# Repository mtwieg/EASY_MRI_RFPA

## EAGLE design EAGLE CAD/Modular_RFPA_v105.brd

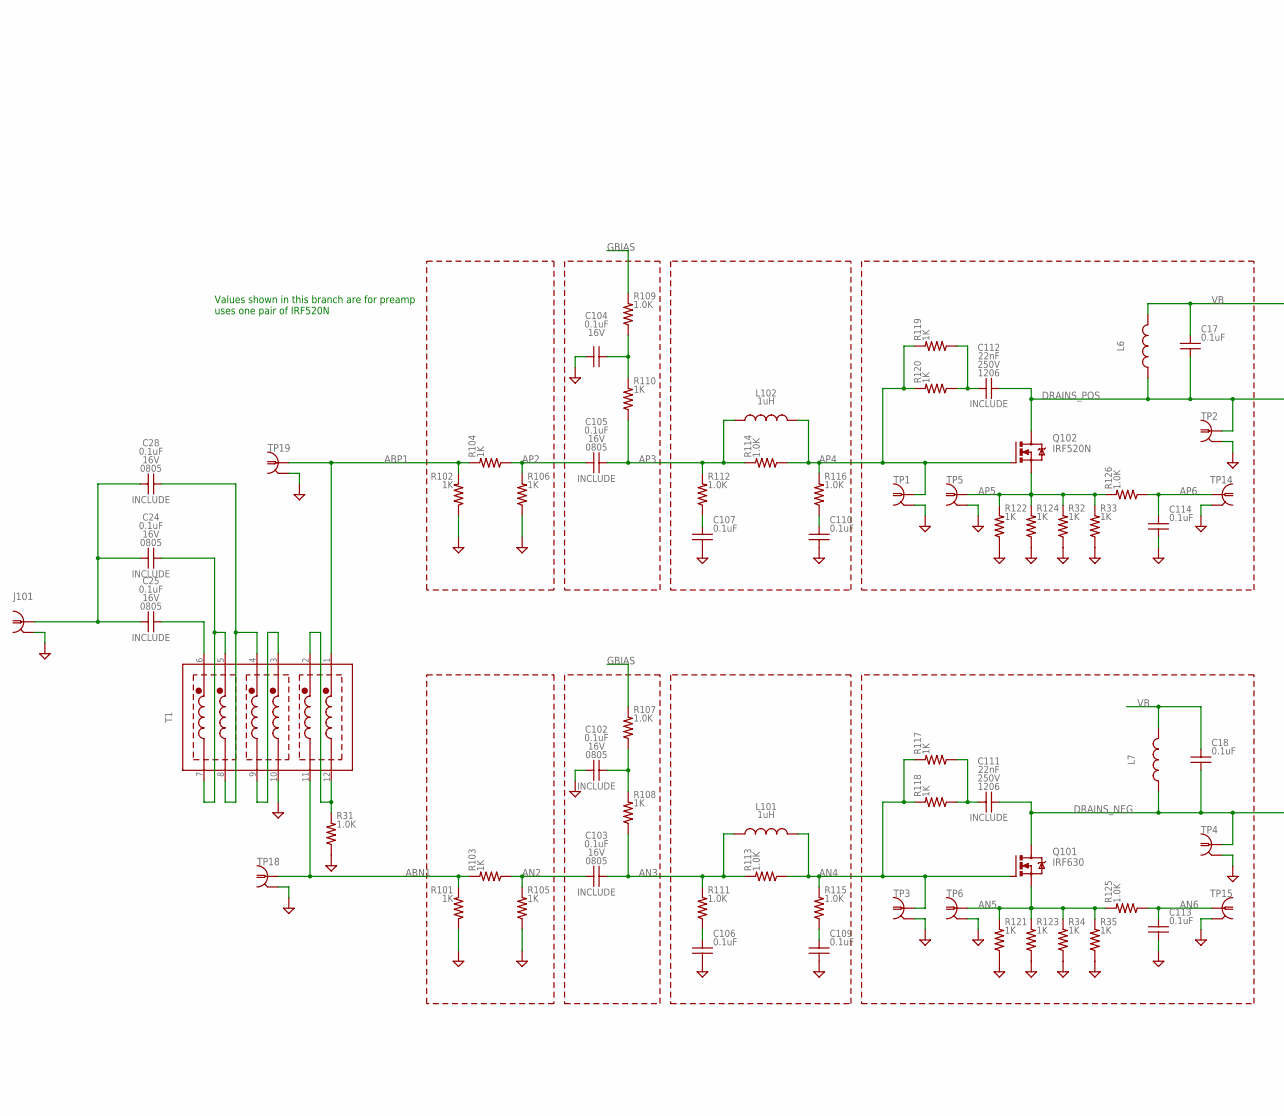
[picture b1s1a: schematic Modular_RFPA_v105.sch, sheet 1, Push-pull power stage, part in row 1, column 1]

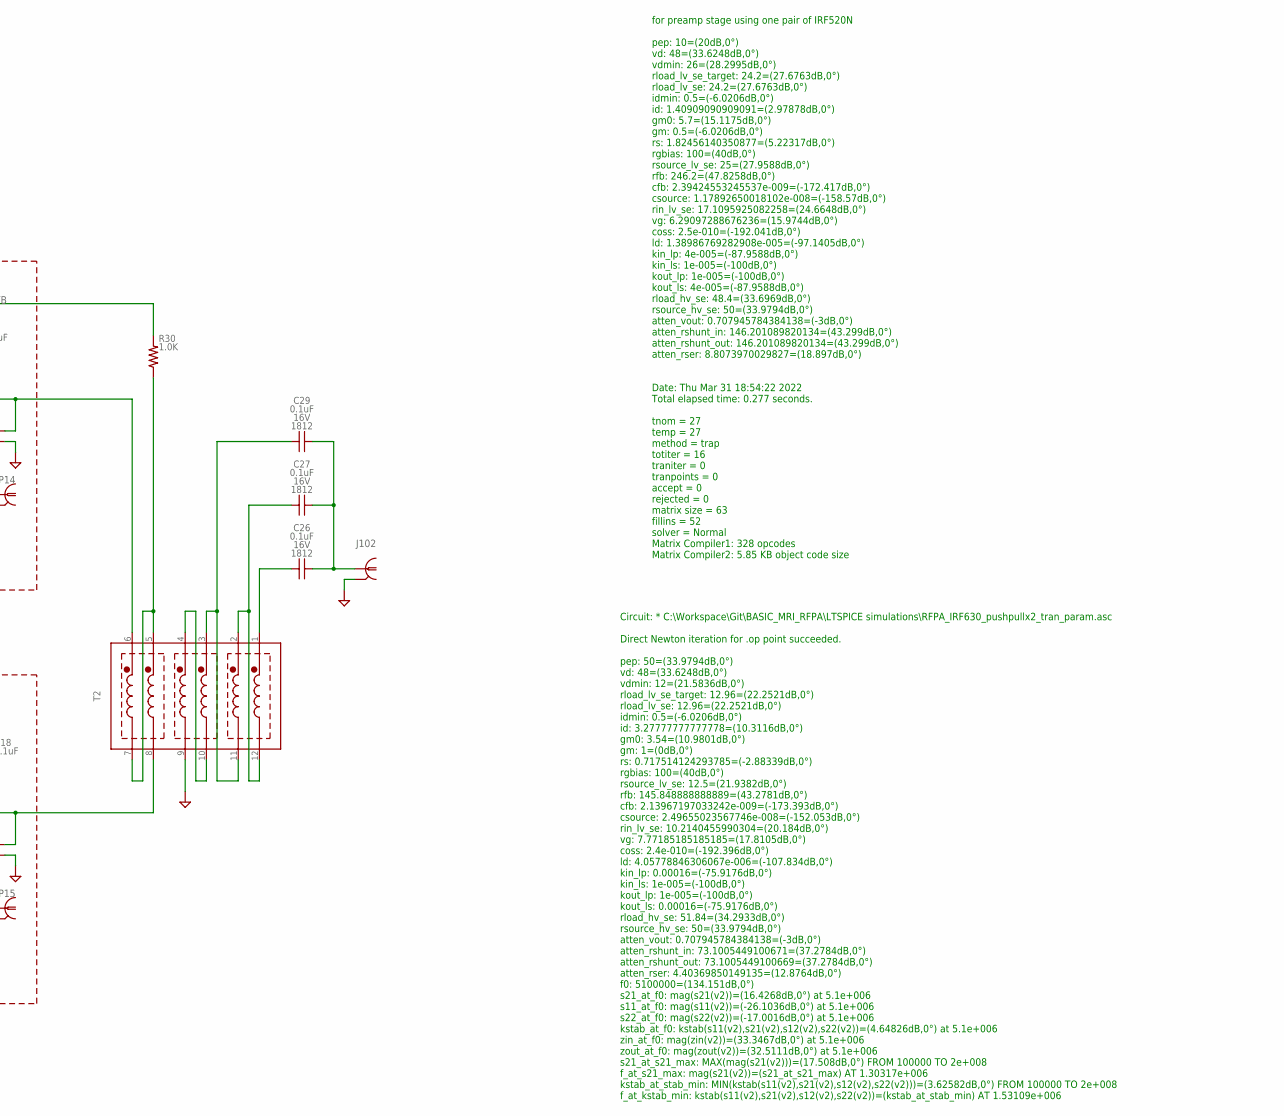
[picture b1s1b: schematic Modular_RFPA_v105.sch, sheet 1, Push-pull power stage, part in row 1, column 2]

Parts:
C17, C18, C26, C27, C29: 0.1uF; C1812
C24, C25, C28, C102, C103, C104, C105, C106, C107, C109, C110, C113, C114: 0.1uF; 0805_IPC-7351B
C111, C112: 22nF; C1206
J101, J102: COAXBNC_EDGE; BNC_EDGE
L6, L7: L; DR127
L101, L102: 1uH; L1008
Q101: IRF630; TO220BV
Q102: IRF520N; TO220BV
R30, R31, R107, R109, R111, R112, R113, R114, R115, R116, R125, R126: 1.0K; 0805_IPC-7351B
R32, R33, R34, R35, R117, R118, R119, R120, R121, R122, R123, R124: 1K; R2512
R101, R102, R103, R104, R105, R106, R108, R110: 1K; R1206
T1, T2: HP4_TRAFO; HP4
TP1, TP3, TP14, TP15, TP18, TP19: PROBE_TPTP_5MM; PROBE_TP_5MM
TP2, TP4, TP5, TP6: PROBE_TPTP_7P5MM; PROBE_TP_7P5MM

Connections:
ABN1: R101.1, R103.1, T1.11 (F2), TP18.TP (1); also elsewhere on the board
ABP1: R102.1, R104.1, T1.1 (S1), TP19.TP (1); also elsewhere on the board
AN2: C103.2, R103.2, R105.1
AN3: C103.1, L101.1, R108.2, R111.1, R113.1
AN4: L101.2, Q101.G, R113.2, R115.1, R117.1, R118.1, TP3.TP (1)
AN5: Q101.S, R34.1, R35.1, R121.1, R123.1, R125.1, TP6.TP (1)
AN6: C113.1, R125.2, TP15.TP (1)
AP2: C105.2, R104.2, R106.1
AP3: C105.1, L102.1, R110.2, R112.1, R114.1
AP4: L102.2, Q102.G, R114.2, R116.1, R119.1, R120.1, TP1.TP (1)
AP5: Q102.S, R32.1, R33.1, R122.1, R124.1, R126.1, TP5.TP (1)
AP6: C114.1, R126.2, TP14.TP (1)
DRAINS_NEG: C18.2, C111.2, L7.1, Q101.D, T2.8 (F5), TP4.TP (1); also elsewhere on the board
DRAINS_POS: C17.2, C112.2, L6.1, Q102.D, T2.6 (S6), TP2.TP (1); also elsewhere on the board
GBIAS: R107.1, R109.1; also elsewhere on the board
GND: C102.2, C104.2, C106.2, C107.2, C109.2, C110.2, C113.2, C114.2, J101.G1 (GND1), J101.G2 (GND1), J101.G3 (GND1), J101.G4 (GND1), J102.G1 (GND1), J102.G2 (GND1), J102.G3 (GND1), J102.G4 (GND1), R31.2, R32.2, R33.2, R34.2, R35.2, R101.2, R102.2, R105.2, R106.2, R121.2, R122.2, R123.2, R124.2, T1.10 (F3), T2.9 (F4), TP1.GND (GND1), TP2.GND (GND1), TP3.GND (GND1), TP4.GND (GND1), TP5.GND (GND1), TP6.GND (GND1), TP14.GND (GND1), TP15.GND (GND1), TP18.GND (GND1), TP19.GND (GND1); also elsewhere on the board
unnamed: C111.1, R117.2, R118.2
unnamed: C106.1, R111.2
unnamed: C104.1, R109.2, R110.1
unnamed: C107.1, R112.2
unnamed: C110.1, R116.2
unnamed: C112.1, R119.2, R120.2
unnamed: C102.1, R107.2, R108.1
unnamed: C109.1, R115.2
unnamed: T1.3 (S3), T1.9 (F4)
unnamed: R31.1, T1.2 (S2), T1.12 (F1)
unnamed: C27.1, T2.2 (S2), T2.12 (F1)
unnamed: C26.1, T2.1 (S1)
unnamed: C26.2, C27.2, C29.2, J102.C (1)
unnamed: C24.2, C25.2, C28.2, J101.C (1)
unnamed: C25.1, T1.6 (S6)
unnamed: C29.1, T2.3 (S3), T2.11 (F2)
unnamed: C28.1, T1.4 (S4), T1.8 (F5)
unnamed: T2.4 (S4), T2.10 (F3)
VB: C17.1, C18.1, L6.2, L7.2, R30.1; also elsewhere on the board
VB_CT: R30.2, T2.5 (S5), T2.7 (F6)
VB_CT1: C24.1, T1.5 (S5), T1.7 (F6)

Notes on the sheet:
for preamp stage using one pair of IRF520N pep: 10=(20dB,0°) vd: 48=(33.6248dB,0°) vdmin: 26=(28.2995dB,0°) rload_lv_se_target: 24.2=(27.6763dB,0°) rload_lv_se: 24.2=(27.6763dB,0°) idmin: 0.5=(-6.0206dB,0°) id: 1.40909090909091=(2.97878dB,0°) gm0: 5.7=(15.1175dB,0°) gm: 0.5=(-6.0206dB,0°) rs: 1.824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
Values shown in this branch are for preamp uses one pair of IRF520N
Circuit: * C:\Workspace\Git\BASIC_MRI_RFPA\LTSPICE simulations\RFPA_IRF630_pushpullx2_tran_param.asc Direct Newton iteration for .op point succeeded. pep: 50=(33.9794dB,0°) vd: 48=(33.6248dB,0°) vdmin: 12=(21.5836dB,0°) rload_lv_se_target: 12.96=(22.2521dB,0°) rload_lv_se: 12.96=(22.2521dB,0°) idmi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

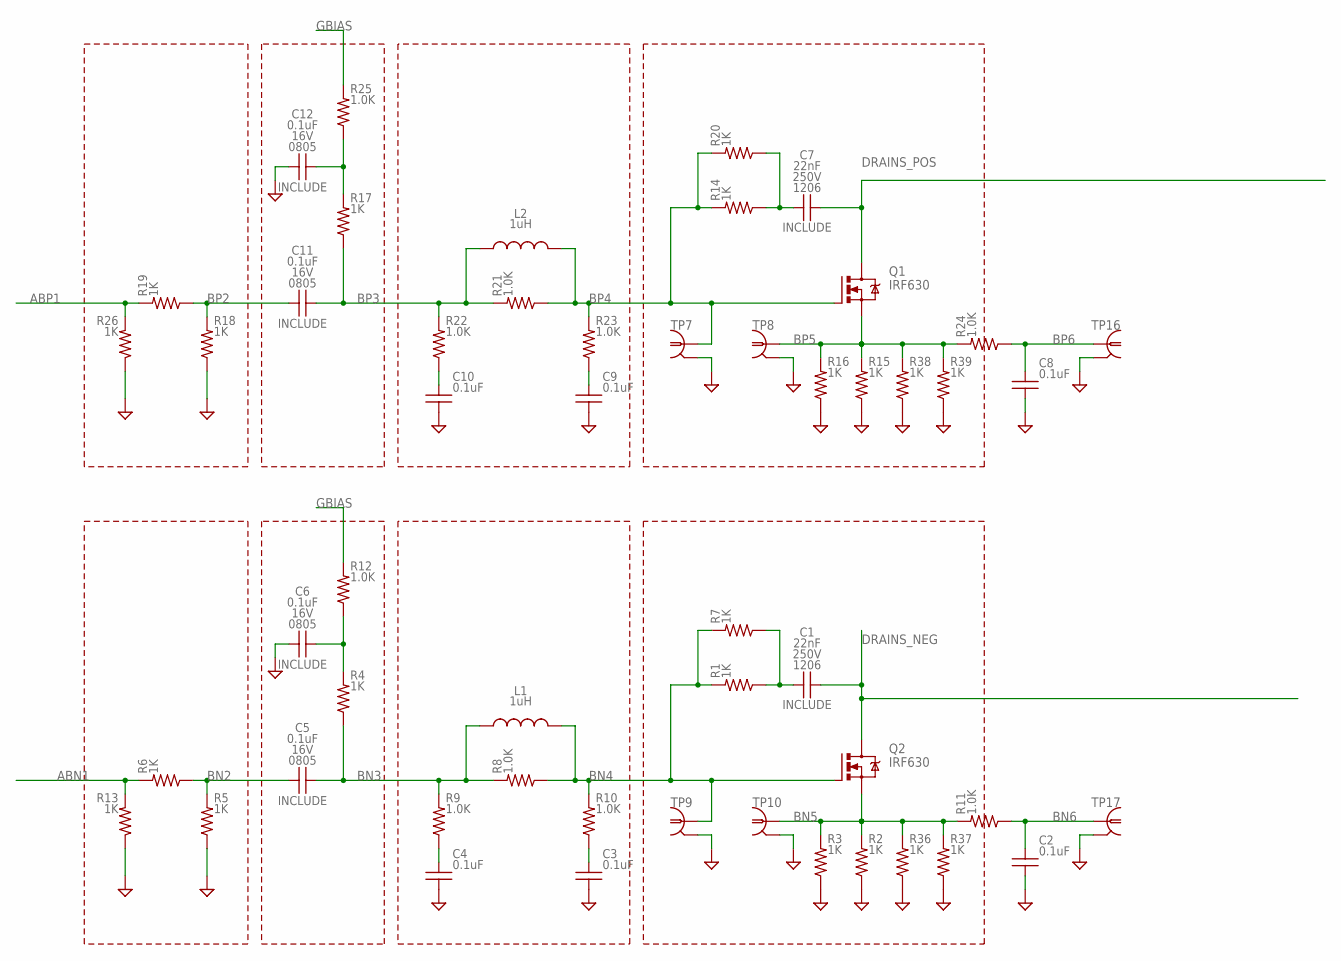
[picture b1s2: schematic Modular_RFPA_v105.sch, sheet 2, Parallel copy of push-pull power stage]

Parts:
C1, C7: 22nF; C1206
C2, C3, C4, C5, C6, C8, C9, C10, C11, C12: 0.1uF; 0805_IPC-7351B
L1, L2: 1uH; L1008
Q1, Q2: IRF630; TO220BV
R1, R2, R3, R7, R14, R15, R16, R20, R36, R37, R38, R39: 1K; R2512
R4, R5, R6, R13, R17, R18, R19, R26: 1K; R1206
R8, R9, R10, R11, R12, R21, R22, R23, R24, R25: 1.0K; 0805_IPC-7351B
TP7, TP9, TP10, TP16: PROBE_TPTP_5MM; PROBE_TP_5MM
TP8, TP17: PROBE_TPTP_7P5MM; PROBE_TP_7P5MM

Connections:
ABN1: R6.1, R13.1; also elsewhere on the board
ABP1: R19.1, R26.1; also elsewhere on the board
BN2: C5.2, R5.1, R6.2
BN3: C5.1, L1.1, R4.2, R8.1, R9.1
BN4: L1.2, Q2.G, R1.1, R7.1, R8.2, R10.1, TP9.TP (1)
BN5: Q2.S, R2.1, R3.1, R11.1, R36.1, R37.1, TP10.TP (1)
BN6: C2.1, R11.2, TP17.TP (1)
BP2: C11.2, R18.1, R19.2
BP3: C11.1, L2.1, R17.2, R21.1, R22.1
BP4: L2.2, Q1.G, R14.1, R20.1, R21.2, R23.1, TP7.TP (1)
BP5: Q1.S, R15.1, R16.1, R24.1, R38.1, R39.1, TP8.TP (1)
BP6: C8.1, R24.2, TP16.TP (1)
DRAINS_NEG: C1.2, Q2.D; also elsewhere on the board
DRAINS_POS: C7.2, Q1.D; also elsewhere on the board
GBIAS: R12.1, R25.1; also elsewhere on the board
GND: C2.2, C3.2, C4.2, C6.2, C8.2, C9.2, C10.2, C12.2, R2.2, R3.2, R5.2, R13.2, R15.2, R16.2, R18.2, R26.2, R36.2, R37.2, R38.2, R39.2, TP7.GND (GND1), TP8.GND (GND1), TP9.GND (GND1), TP10.GND (GND1), TP16.GND (GND1), TP17.GND (GND1); also elsewhere on the board
unnamed: C6.1, R4.1, R12.2
unnamed: C4.1, R9.2
unnamed: C3.1, R10.2
unnamed: C1.1, R1.2, R7.2
unnamed: C12.1, R17.1, R25.2
unnamed: C10.1, R22.2
unnamed: C9.1, R23.2
unnamed: C7.1, R14.2, R20.2

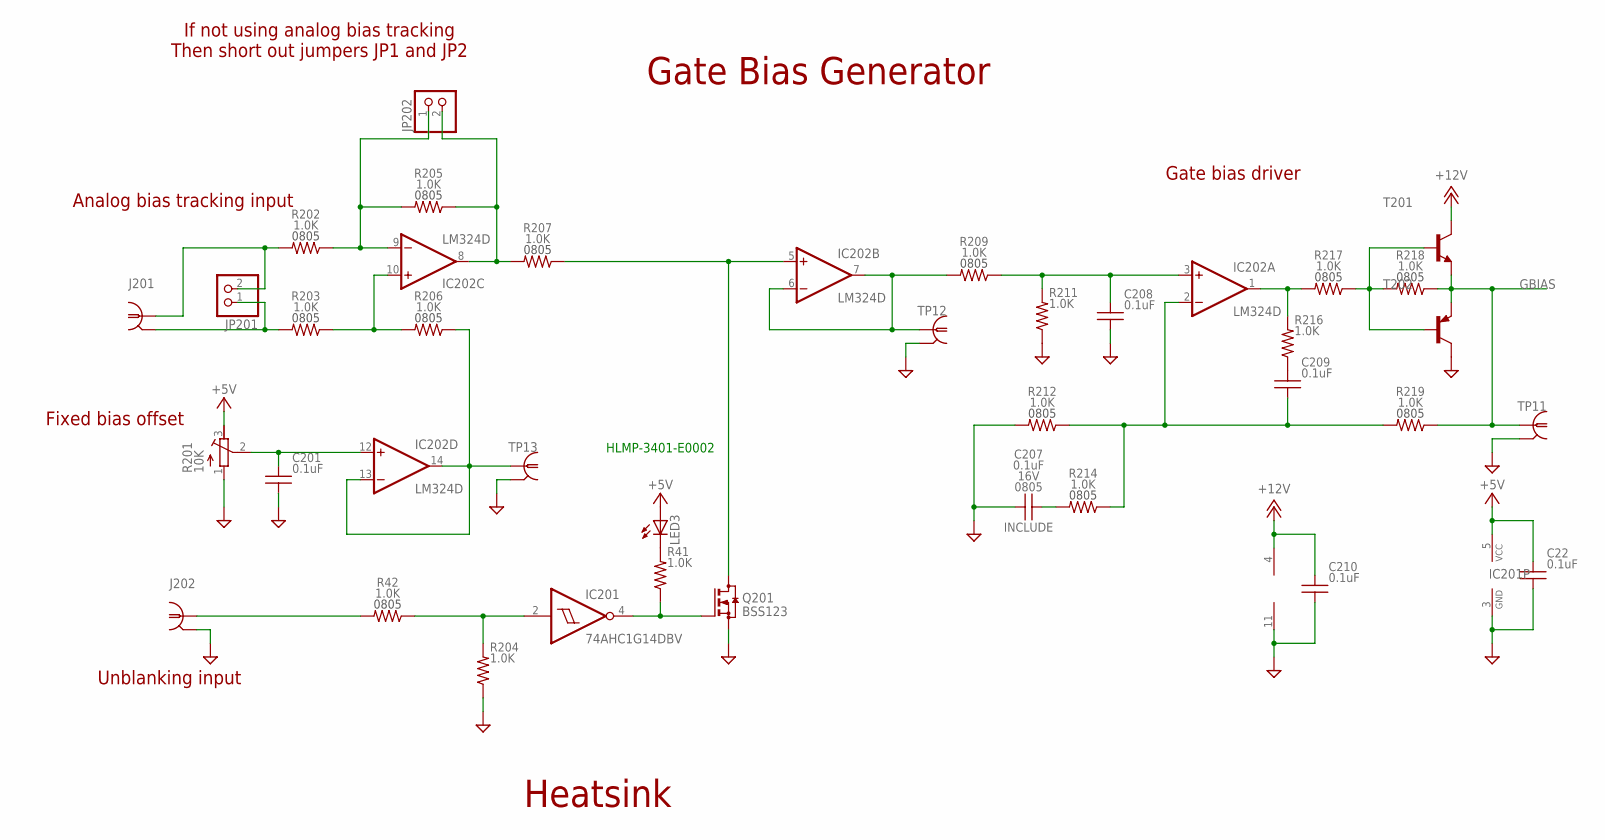
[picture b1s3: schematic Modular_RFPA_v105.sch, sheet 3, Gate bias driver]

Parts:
C22, C201, C207, C208, C209, C210: 0.1uF; 0805_IPC-7351B
IC201: 74AHC1G14DBV; SOT23-5
IC202: LM324D; SO14
J201, J202: COAXBNC_EDGE; BNC_EDGE
JP201, JP202: PINHD-1X2; 1X02
LED3: LED5MM
Q201: BSS123; SOT23
R41, R42, R202, R203, R204, R205, R206, R207, R209, R211, R212, R214, R216, R217, R218, R219: 1.0K; 0805_IPC-7351B
R201: 10K; RTRIM3299W
T201: BC808-NPN-SOT23-BEC; SOT23-BEC
T202: BC807-16-PNP-SOT23-BEC; SOT23-BEC
TP11, TP12, TP13: PROBE_TPTP_5MM; PROBE_TP_5MM

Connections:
+5V: C22.1, IC201.5 (VCC), LED3.A, R201.3 (E); also elsewhere on the board
+12V: C210.1, IC202.4 (V+), T201.C; also elsewhere on the board
GBIAS: R218.2, R219.2, T201.E, T202.E, TP11.TP (1); also elsewhere on the board
GND: C22.2, C201.2, C207.2, C208.2, C210.2, IC201.3 (GND), IC202.11 (V-), J202.G1 (GND1), J202.G2 (GND1), J202.G3 (GND1), J202.G4 (GND1), Q201.2 (S), R201.1 (A), R204.2, R211.2, R212.1, T202.C, TP11.GND (GND1), TP12.GND (GND1), TP13.GND (GND1); also elsewhere on the board
unnamed: IC202.1 (OUT), R216.1, R217.1
unnamed: R217.2, R218.1, T201.B, T202.B
unnamed: IC201.2 (I), R42.2, R204.1
unnamed: IC202.6 (-IN), IC202.7 (OUT), R209.1, TP12.TP (1)
unnamed: C209.1, R216.2
unnamed: C207.1, R214.1
unnamed: C209.2, IC202.2 (-IN), R212.2, R214.2, R219.1
unnamed: C208.1, IC202.3 (+IN), R209.2, R211.1
unnamed: IC202.10 (+IN), R203.2, R206.1
unnamed: IC202.8 (OUT), JP202.2, R205.2, R207.1
unnamed: IC202.9 (-IN), JP202.1, R202.2, R205.1
unnamed: J201.C (1), JP201.2, R202.1
unnamed: J201.G1 (GND1), J201.G2 (GND1), J201.G3 (GND1), J201.G4 (GND1), JP201.1, R203.1
unnamed: IC202.5 (+IN), Q201.3 (D), R207.2
unnamed: IC201.4 (O), Q201.1 (G), R41.2
unnamed: C201.1, IC202.12 (+IN), R201.2 (S)
unnamed: IC202.13 (-IN), IC202.14 (OUT), R206.2, TP13.TP (1)
unnamed: LED3.K (C), R41.1
unnamed: J202.C (1), R42.1

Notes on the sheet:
Gate Bias Generator
Heatsink
If not using analog bias tracking Then short out jumpers JP1 and JP2
Analog bias tracking input
Fixed bias offset
Gate bias driver
Unblanking input
‎HLMP-3401-E0002‎

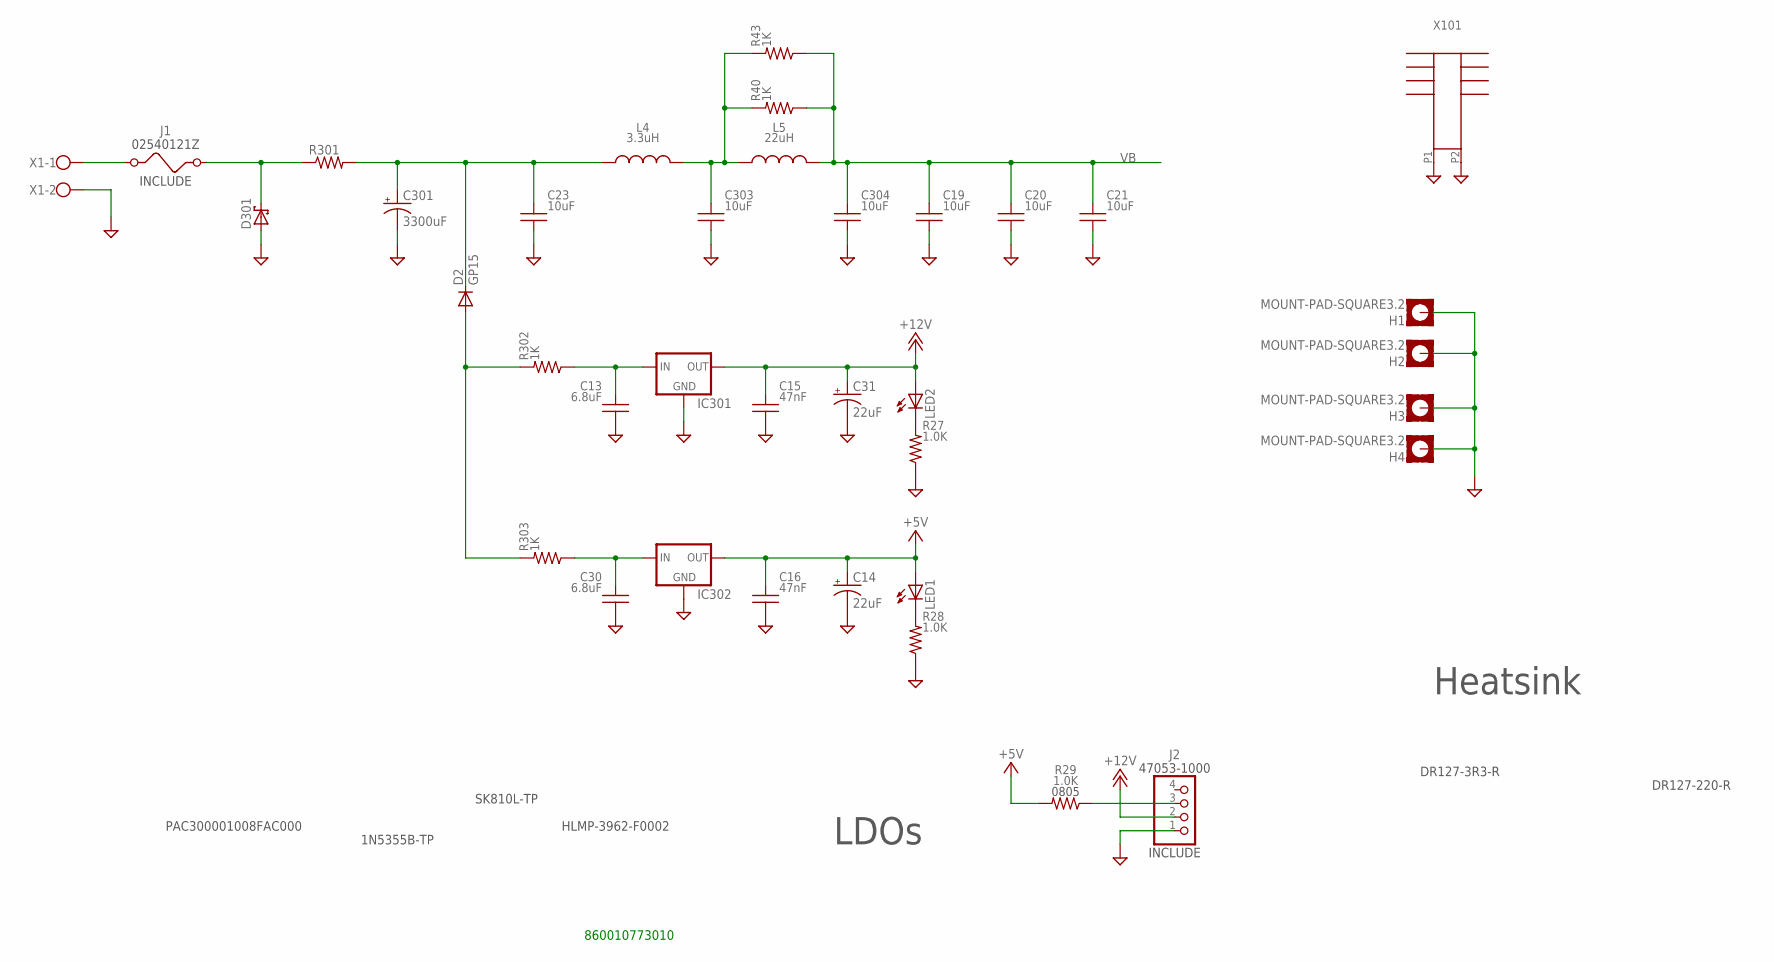
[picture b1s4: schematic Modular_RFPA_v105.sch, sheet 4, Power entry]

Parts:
C13, C30: 6.8uF; C1210
C14, C31: 22uF; E2,5-7
C15, C16: 47nF; C1206
C19, C20, C21, C23, C303, C304: 10uF; C2220_CKG57N
C301: 3300uF; EB25D
D2: GP15; DO15-12
D301: SCHOTTKY-DIODESMC; SMC
H1, H2, H3, H4: MOUNT-PAD-SQUARE3.2; 3,2-PAD-SQUARE
IC301, IC302: 78XXS
J1: FUSE_2P; 02540121Z
J2: KK_PCFAN; 47053-1000
L4: 3.3uH; DR127
L5: 22uH; DR127
LED1, LED2: LED5MM
R27, R28, R29: 1.0K; 0805_IPC-7351B
R40, R43, R302, R303: 1K; R1206
R301: R-US_0817/7V; P0817V
X1: W237-102
X101: HEATSINK_OMNI_DUAL30-75-D; OMNI-UNI-30-75-D

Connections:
+5V: C14.+, C16.1, IC302.OUT, LED1.A, R29.1; also elsewhere on the board
+12V: C15.1, C31.+, IC301.OUT, J2.2, LED2.A; also elsewhere on the board
GND: C13.2, C14.-, C15.2, C16.2, C19.2, C20.2, C21.2, C23.2, C30.2, C31.-, C301.-, C303.2, C304.2, D301.A, H1.B3,2, H2.B3,2, H3.B3,2, H4.B3,2, IC301.GND, IC302.GND, J2.1, R27.2, R28.2, X1.2, X101.P1, X101.P2; also elsewhere on the board
unnamed: D2.A, R302.1, R303.1
unnamed: LED2.K (C), R27.1
unnamed: LED1.K (C), R28.1
unnamed: C13.1, IC301.IN, R302.2
unnamed: D301.C, J1.2, R301.1
unnamed: J1.1, X1.1
unnamed: C23.1, C301.+, D2.C, L4.1, R301.2
unnamed: C303.1, L4.2, L5.1, R40.1, R43.1
unnamed: C30.1, IC302.IN, R303.2
unnamed: J2.3, R29.2
VB: C19.1, C20.1, C21.1, C304.1, L5.2, R40.2, R43.2; also elsewhere on the board

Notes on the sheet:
LDOs
Heatsink
PAC300001008FAC000
DR127-220-R
DR127-3R3-R
1N5355B-TP
HLMP-3962-F0002‎
860010773010
SK810L-TP

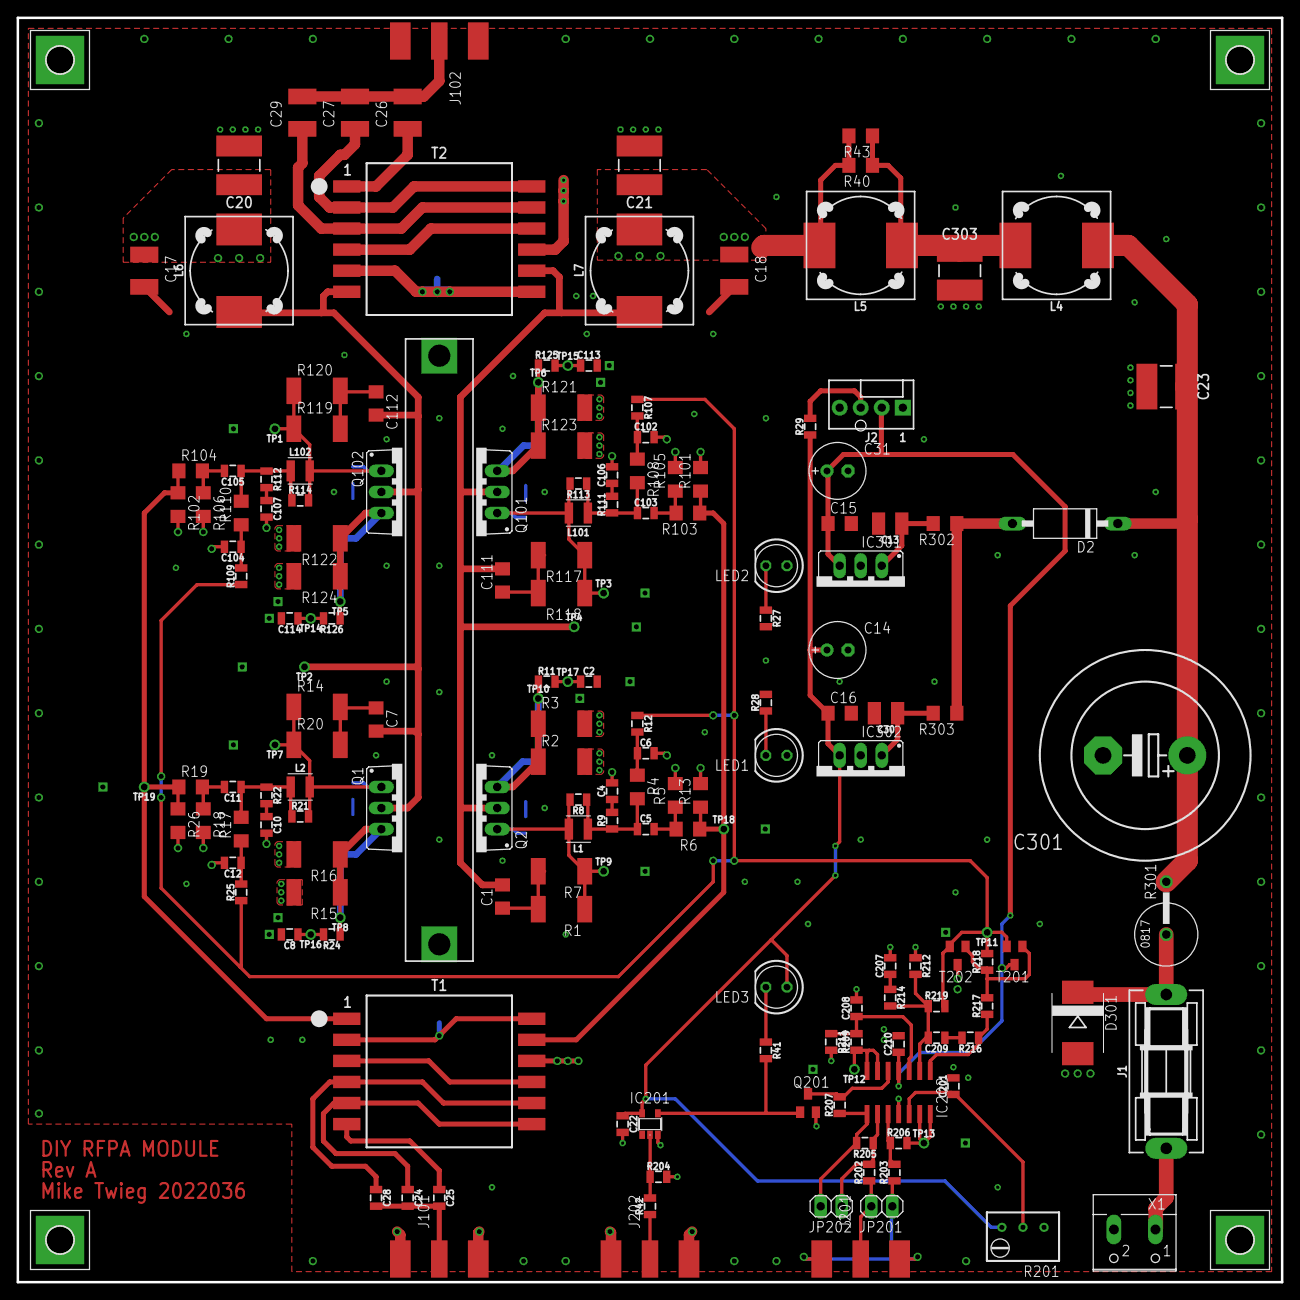
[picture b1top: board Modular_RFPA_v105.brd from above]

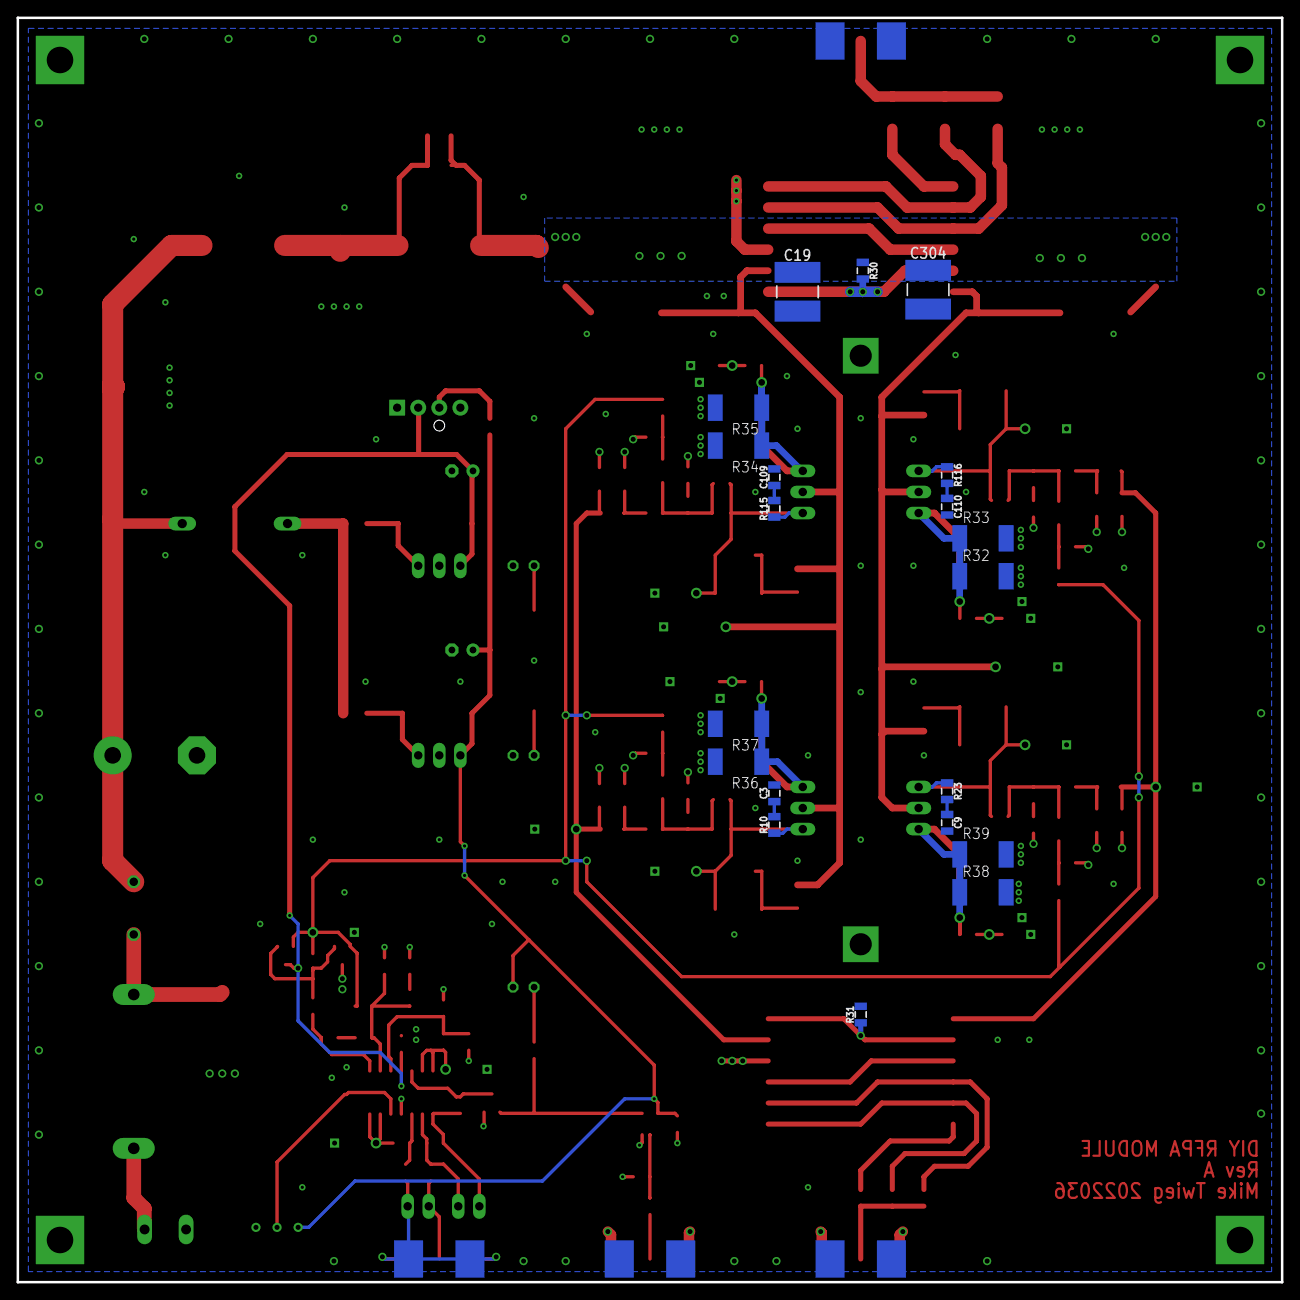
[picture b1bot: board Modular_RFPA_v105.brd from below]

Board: 4 copper layers, 152.4 x 152.4 mm, 197 parts (20 on the bottom side), 86 nets.
